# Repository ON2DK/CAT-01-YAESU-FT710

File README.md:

# CAT-01 YAESU FT-710

CAT-01 is a radio-specific CAT interface for connecting the **ESP32 CW Keyer V2** universal 3.3 V UART CAT port to the **Yaesu FT-710 CAT-3** interface.

> **Project status:** PCB production files completed. Hardware testing with the assembled PCB and FT-710 is still pending.

## Purpose

The ESP32 CW Keyer V2 uses 3.3 V UART levels on its universal CAT connector. The FT-710 CAT-3 interface uses 5 V TTL levels. CAT-01 provides the required interface between both devices.

The design uses an **SN74HCT125N** powered from 5 V for the Keyer-to-radio path and a resistor divider for the radio-to-Keyer path.

## Connections

### J1 — KEYER_CAT

| Signal | Function |
|---|---|
| +5V | Power for CAT-01 |
| KEYER_RX_3V3 | CAT data from radio to Keyer |
| KEYER_TX_3V3 | CAT data from Keyer to radio |
| GND | Ground |

Always follow the **signal names printed on the final PCB silkscreen** when wiring the connector.

### J2 — FT-710 CAT-3

| CAT-01 signal | FT-710 TUNER/LINEAR CAT-3 connection |
|---|---|
| GND | Pin 3 — GND |
| FT710_TXD_5V | Pin 4 — TXD from FT-710 |
| FT710_RXD_5V | Pin 5 — RXD to FT-710 |

**Important:** FT-710 TUNER/LINEAR **pin 1 (+13 V) must not be connected to CAT-01**.

## Signal paths

**Keyer → FT-710**

`KEYER_TX_3V3 → SN74HCT125N → R3 100 Ω → FT710_RXD_5V → FT-710`

**FT-710 → Keyer**

`FT710_TXD_5V → R1/R2 level divider → KEYER_RX_3V3 → ESP32 CW Keyer V2`

## Main components

| Reference | Value / type |
|---|---|
| U1 | SN74HCT125N, DIP-14 |
| C1 | 100 nF |
| R1 | 10 kΩ |
| R2 | 20 kΩ |
| R3 | 100 Ω |
| R4 | 1 kΩ |
| D1 | Power LED |

## Repository layout

The project will contain:

- `KiCad/` — editable KiCad schematic, PCB and project files
- `Gerbers/` — final manufacturing Gerber/drill package
- `Documentation/` — connection and production documentation
- `Photos/` — photographs of the assembled/tested adapter when available

## Manufacturing status

The final KiCad design was checked with:

- 0 DRC violations
- 0 unconnected items
- 0 schematic parity issues

A final visual PCB inspection was also performed and the routing near a via was corrected before regenerating the manufacturing files.

The Gerber package includes front/back copper, front/back solder mask, front/back silkscreen, Edge.Cuts, PTH drill, NPTH drill and Gerber job data.

## Hardware verification

The PCB has been sent for manufacture. The design should therefore currently be treated as **production files completed / hardware test pending**.

After the first assembled CAT-01 has been tested with the ESP32 CW Keyer V2 and a Yaesu FT-710, this section will be updated with the measured/test results and photographs.

## Related project

CAT-01 is intended to be used with the **ESP32 CW Keyer V2**. The Keyer keeps a universal CAT connector so that separate radio-specific adapters can be developed without changing the complete Keyer PCB.

## Disclaimer

This is an amateur-radio DIY hardware project. Verify connector pinout, supply voltage and signal levels before connecting the adapter to a transceiver. In particular, do not connect the FT-710 +13 V pin to CAT-01.

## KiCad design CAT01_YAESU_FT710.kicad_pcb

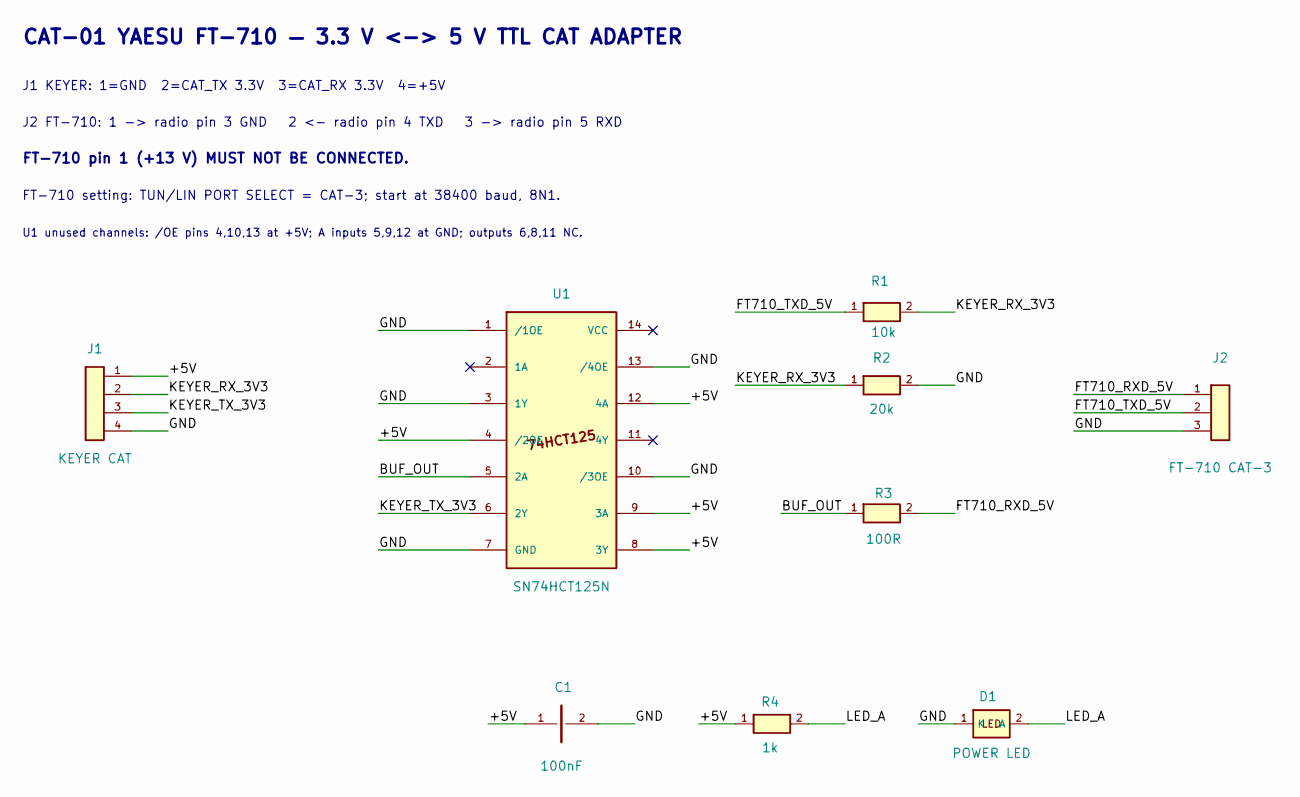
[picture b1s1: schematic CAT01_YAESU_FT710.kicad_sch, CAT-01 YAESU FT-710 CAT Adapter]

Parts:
C1: 100nF; C_DISC_3
D1: POWER LED; LED_4
J1: KEYER CAT; J1_4P
J2: FT-710 CAT-3; J2_3P
R1: 10k; R_AXIAL_10
R2: 20k; R_AXIAL_10
R3: 100R; R_AXIAL_10
R4: 1k; R_AXIAL_10
U1: SN74HCT125N; DIP14_762

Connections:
/+5V: C1.1, J1.1, R4.1, U1.4 (/2OE), U1.8 (3Y), U1.9 (3A), U1.12 (4A)
/BUF_OUT: R3.1, U1.5 (2A)
/FT710_RXD_5V: J2.1, R3.2
/FT710_TXD_5V: J2.2, R1.1
/GND: C1.2, D1.1 (K), J1.4, J2.3, R2.2, U1.1 (/1OE), U1.3 (1Y), U1.7 (GND), U1.10 (/3OE), U1.13 (/4OE)
/KEYER_RX_3V3: J1.2, R1.2, R2.1
/KEYER_TX_3V3: J1.3, U1.6 (2Y)
/LED_A: D1.2 (A), R4.2

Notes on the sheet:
U1 unused channels: /OE pins 4,10,13 at +5V; A inputs 5,9,12 at GND; outputs 6,8,11 NC.
J2 FT-710: 1 -> radio pin 3 GND 2 <- radio pin 4 TXD 3 -> radio pin 5 RXD
CAT-01 YAESU FT-710 — 3.3 V <-> 5 V TTL CAT ADAPTER
J1 KEYER: 1=GND 2=CAT_TX 3.3V 3=CAT_RX 3.3V 4=+5V
FT-710 pin 1 (+13 V) MUST NOT BE CONNECTED.
FT-710 setting: TUN/LIN PORT SELECT = CAT-3; start at 38400 baud, 8N1.

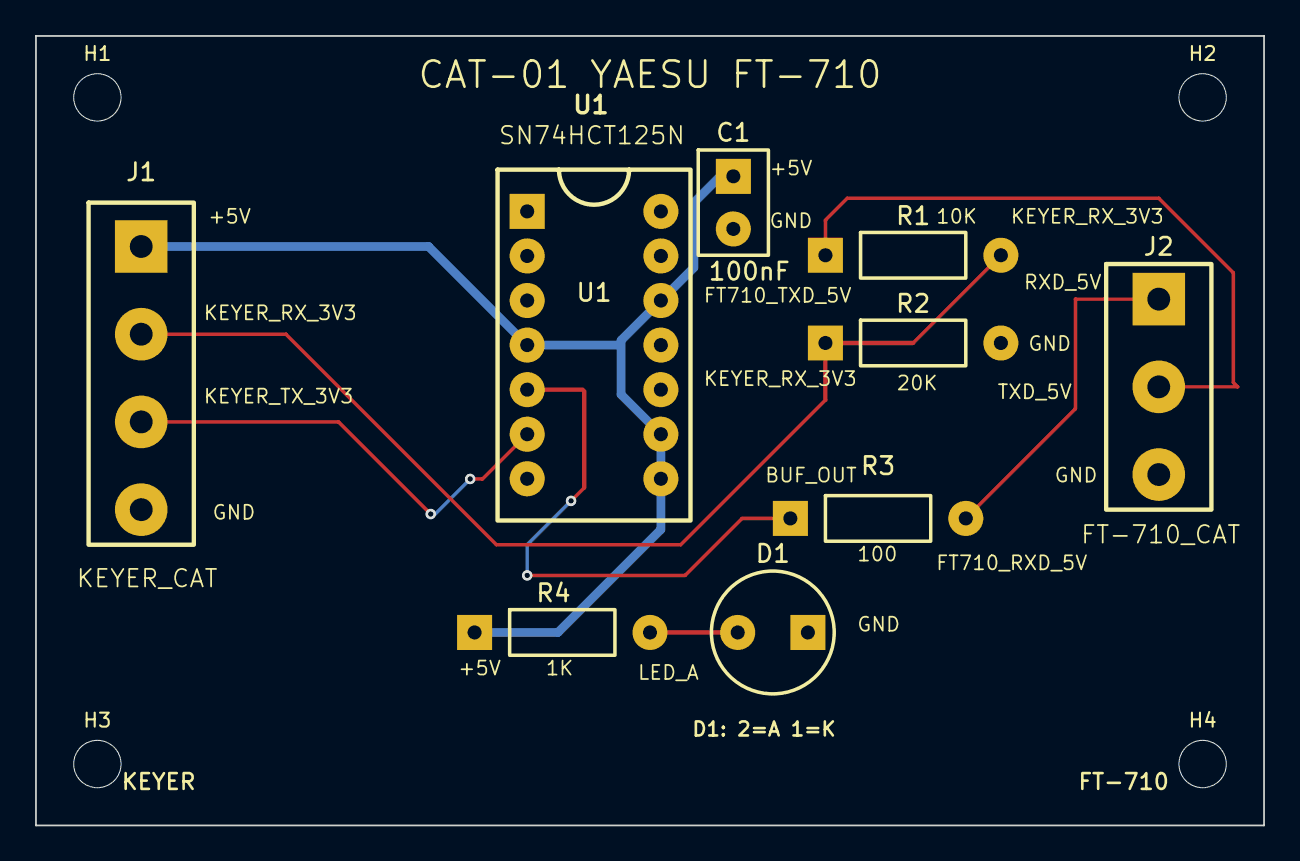
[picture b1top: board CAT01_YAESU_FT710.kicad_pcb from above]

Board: 2 copper layers, 70.0 x 45.0 mm, 13 parts (0 on the bottom side), 8 nets.

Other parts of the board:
H1, H2, H3, H4: M2.5; MOUNT_M2_5
